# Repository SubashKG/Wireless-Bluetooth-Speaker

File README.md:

View this project on [CADLAB.io](https://cadlab.io/project/29113). 

# Wireless-Bluetooth-Speaker

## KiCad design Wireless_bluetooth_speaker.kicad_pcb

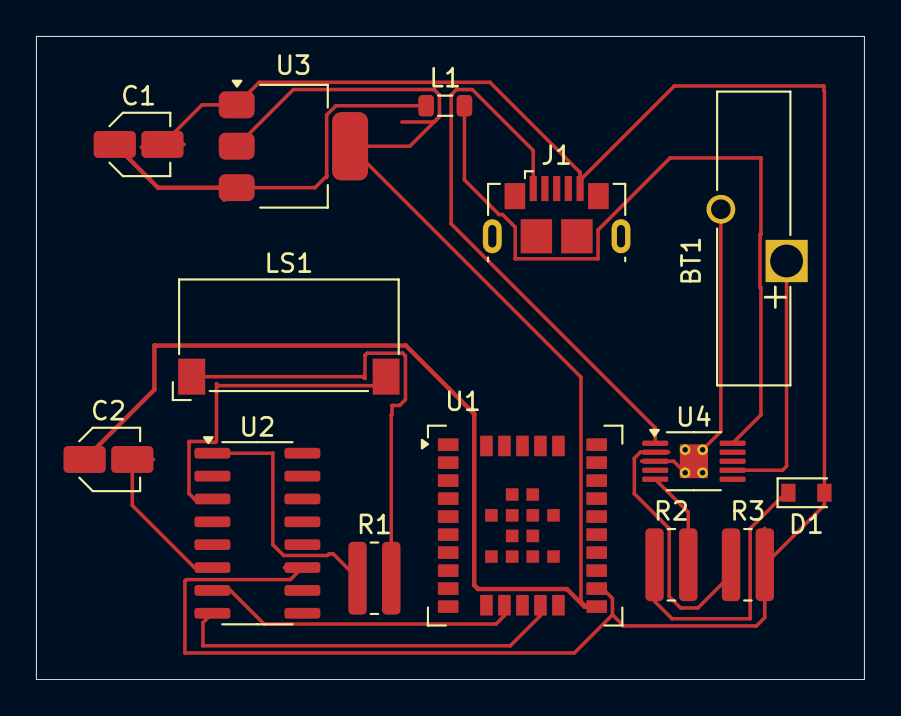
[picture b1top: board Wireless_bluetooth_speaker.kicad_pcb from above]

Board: 2 copper layers, 46.0 x 35.7 mm, 14 parts (0 on the bottom side), 16 nets.

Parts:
BT1: Battery; Battery_Panasonic_CR1632-V1AN_Vertical_CircularHoles
C1: 10uF; C_Elec_3x5.4
C2: 100nF; C_Elec_3x5.4
D1: LED; LED_miniPLCC_2315
J1: USB_B_Micro; USB_Micro-B_GCT_USB3076-30-A
L1: 10uH; L_0805_2012Metric
LS1: Speaker; Speaker_CUI_CMR-1206S-67
R1: 10k; R_0815_2038Metric
R2, R3: 1k; R_0815_2038Metric
U1: BTM112; NINA-B111
U2: PAM8403D; SOP-16_3.9x9.9mm_P1.27mm
U3: AMS1117-5.0; SOT-223-3_TabPin2
U4: BQ24090DGQ; HVSSOP-10-1EP_3x3mm_P0.5mm_EP1.57x1.88mm_ThermalVias

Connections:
+12V: C1.1, L1.1, U3.3 (VI)
GND: C1.2, D1.2 (A), J1.5 (GND), R3.2, U1.17 (GND), U2.11 (GND), U3.1 (GND)
unnamed: BT1.1 (+), U4.7 (ISET2)
unnamed: BT1.2 (-), U4.3 (VSS), U4.11 (VSS)
unnamed: D1.1 (K), R2.1
unnamed: J1.1 (VBUS), U4.1 (IN)
unnamed: LS1.1, R1.2
unnamed: U1.14 (UART_RX), U2.8 (VREF)
unnamed: U1.12 (UART_TX), U2.7 (INL)
unnamed: C2.1, U1.16 (VCC), U3.2 (VO)
unnamed: R1.1, U2.1 (LOUT+)
unnamed: LS1.2, U2.3 (LOUT-)
unnamed: C2.2, U2.6 (VDD)
unnamed: R3.1, U4.2 (ISET)
unnamed: L1.2, U4.10 (OUT)
unnamed: R2.2, U4.5 (~PG)

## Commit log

2025-04-01 Backlink to CADLAB.io has been added.
2025-04-01 KiCad project
